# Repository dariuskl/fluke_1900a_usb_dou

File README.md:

# PCB

The latest PCB revision that has been produced and tested is rev. 0. However,
there is an error in that version: Rx and Tx are swapped (of course!) on the
USB side. That can be fixed with a bodge, but later commits fix that mistake
without making functional changes.

# Firmware

The latest firmware version that has been tested is 0.1.0.0. There are no known
issues.

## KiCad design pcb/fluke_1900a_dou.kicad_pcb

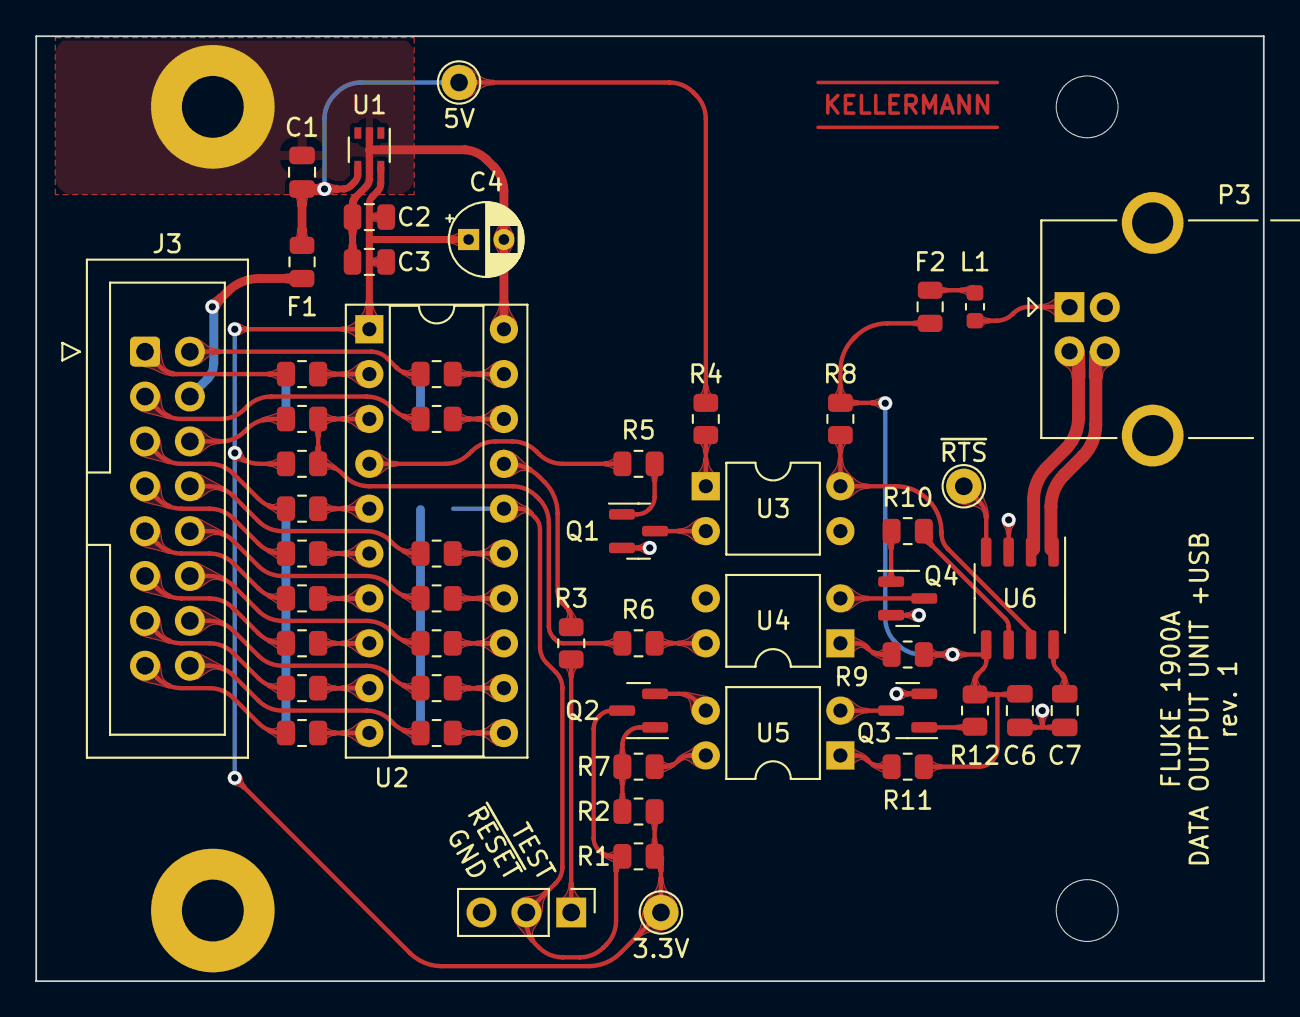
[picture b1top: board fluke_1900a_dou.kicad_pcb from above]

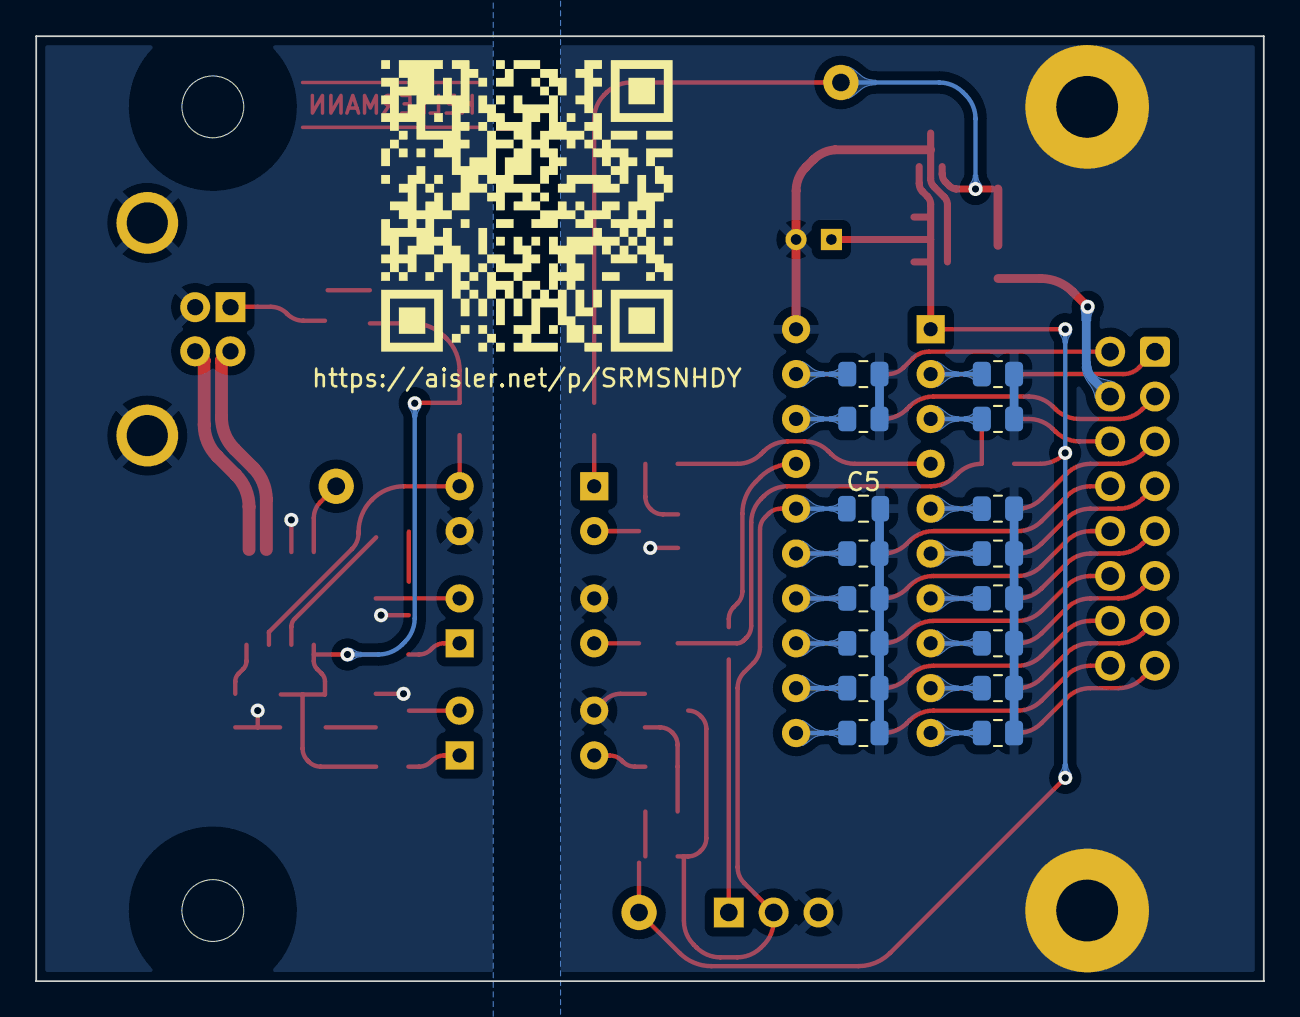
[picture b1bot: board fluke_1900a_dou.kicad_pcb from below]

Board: 2 copper layers, 69.5 x 53.5 mm, 74 parts (17 on the bottom side), 60 nets.

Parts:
C1, C3, C6, C7: 100n; C_0805_2012Metric
C2: 470n; C_0805_2012Metric
C4: 10u/10V; CP_Radial_D4.0mm_P2.00mm
C5: 2.2nF 0805; C_0805_2012Metric
F1, F2: 100mA 0805; Fuse_0805_2012Metric
H1, H2: 3,5mm; MountingHole_3.5mm_Pad
H3, H4: 3,5mm; MountingHole_3.5mm
J3: DOU CONNECTOR; IDC-Header_2x08_P2.54mm_Vertical
L1: 600R 1A 0603; L_0603_1608Metric
P3: USB_B; USB_B_OST_USB-B1HSxx_Horizontal
Q1, Q2, Q3, Q4: Si2336DS; SOT-23
QR1: https://aisler.net/p/SRMSNHDY; Aisler_QR
R1: 47k; R_0805_2012Metric
R2: 100k; R_0805_2012Metric
R3: 330; R_0805_2012Metric
R4, R9, R11: 390R 0805; R_0805_2012Metric
R5, R6, R7, R10, R12: 0; R_0805_2012Metric
R8: 4k7; R_0805_2012Metric
R13: DNP; R_0805_2012Metric
R20, R21, R22, R24, R25, R26, R27, R28, R29, R30, R31, R32, R33, R34, R35, R36, R37, R38, R39, R40, R41, R42, R43, R44, R45, R46, R47, R48, R49, R50: 1.2M 0805; R_0805_2012Metric
TP1: 5V; TestPoint_THTPad_D2.0mm_Drill1.0mm
TP2: 3.3V; TestPoint_THTPad_D2.0mm_Drill1.0mm
TP3: ~{RTS}; TestPoint_THTPad_D2.0mm_Drill1.0mm
U1: TPS71533; SOT-353_SC-70-5
U2: MSP430G2452IN20; DIP-20_W7.62mm_Socket
U3, U4, U5: SFH617A-4; DIP-4_W7.62mm
U6: CH340N; SOP-8_3.9x4.9mm_P1.27mm
X1: DEBUG; PinHeader_1x03_P2.54mm_Vertical

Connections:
+3V3: C2.1, C3.1, C4.1, R1.2, R2.2, R13.1, TP2.1, U1.5 (OUT), U2.1 (DVCC)
+5V: C1.1, F1.1, R4.1, TP1.1, U1.4 (IN)
/AS_1: R6.2, R13.2, R25.1, R45.1, U2.3 (TA0.0/CA1/A1/P1.1)
/AS_2: R27.1, R46.1, U2.15 (TDO/TDI/SDI/SDA/CAOUT/CA7/A7/P1.7)
/AS_3: R29.1, R47.1, U2.14 (TDI/TCLK/TA0.1/SDO/SCL/CA6/A6/P1.6)
/AS_4: R31.1, R48.1, U2.13 (P2.5)
/AS_5: R33.1, R49.1, U2.12 (P2.4)
/AS_6: R35.1, R50.1, U2.11 (P2.3)
/D+: P3.3 (D+), U6.1 (UD+)
/D-: P3.2 (D-), U6.2 (UD-)
/DS: R22.1, R42.1, U2.18 (P2.7/XOUT)
/OUT_A: R21.1, R44.1, U2.19 (P2.6/XIN/TA0.1)
/OUT_B: R20.2, R43.1, U2.2 (TA0CLK/ACLK/CA0/A0/P1.0)
/OUT_C: R32.2, R37.1, U2.9 (P2.1)
/OUT_D: R34.2, R36.1, U2.10 (P2.2)
/OVFL: R28.2, R39.1, U2.7 (TMS/SCLK/TA0.0/CA5/A5/P1.5)
/RESET: Q2.1 (G), R2.1, R7.2
/RNG_2: R24.2, R41.1, U2.5 (ADC10CLK/VREF-/VeREF-/CAOUT/CA3/A3/P1.3)
/RXD: R8.1, U3.4, U6.7 (RXD)
/Rx: R6.1, U4.4
/SBWTCK: R3.2, X1.1
/TXD: R10.1, U6.6 (TXD)
/Tx: R5.1, U2.4 (TA0.1/CA2/A2/P1.2)
/~ML: R26.2, R40.1, U2.6 (TCK/SMCLK/TA0.2/VREF+/VeREF+/CA4/A4/P1.4)
/~MUP: R30.2, R38.1, U2.8 (P2.0)
/~RESET: C5.1, Q2.3 (D), R1.1, U2.16 (~RST/NMI/SBWTDIO), X1.2
GND: C1.2, C2.2, C3.2, C4.2, C5.2, H1.1, H2.1, Q1.2 (S), Q2.2 (S), R36.2, R37.2, R38.2, R39.2, R40.2, R41.2, R42.2, R43.2, R44.2, R45.2, R46.2, R47.2, R48.2, R49.2, R50.2, U1.2 (GND), U2.20 (DVSS), U4.3, U5.3, X1.3
GND1: C6.1, C7.2, P3.4 (GND), P3.5 (Shield), Q3.2 (S), Q4.2 (S), U3.3, U6.3 (GND)
unnamed: C7.1, U6.8 (V3)
unnamed: F1.2, J3.4
unnamed: J3.1, R20.1
unnamed: J3.2, R21.2
unnamed: J3.3, R22.2
unnamed: J3.5, R24.1
unnamed: J3.6, R25.2
unnamed: J3.8, R27.2
unnamed: J3.9, R28.1
unnamed: J3.10, R29.2
unnamed: J3.11, R30.1
unnamed: J3.12, R31.2
unnamed: J3.13, R32.1
unnamed: J3.14, R33.2
unnamed: J3.15, R34.1
unnamed: J3.16, R35.2
unnamed: F2.1, L1.1
unnamed: L1.2, P3.1 (VBUS)
unnamed: Q1.1 (G), R5.2
unnamed: Q1.3 (D), U3.2
unnamed: Q3.1 (G), R12.2
unnamed: Q3.3 (D), U5.2
unnamed: Q4.1 (G), R10.2
unnamed: Q4.3 (D), U4.2
unnamed: R3.1, U2.17 (SBWTCK/TEST)
unnamed: R4.2, U3.1
unnamed: R7.1, U5.4
unnamed: R9.2, U4.1
unnamed: R11.2, U5.1
unnamed: J3.7, R26.1
unnamed: TP3.1, U6.4 (~RTS)
VBUS: C6.2, F2.2, R8.2, R9.1, R11.1, R12.1, U6.5 (VCC)

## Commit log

2022-04-13 initial revision of the PCB finished and ordered
2022-05-03 Tx must be connected to RXD on the CH340N
2022-05-03 add pull-up R13 to Rx line
    While the Rx line is currently not usable, it should be able to operate
    at the same bitrate as the Tx line. That requires the ability to select
    the pull-up accordingly.
2022-05-03 add fuses F1, F2 to protect device and USB host
    In case in anything ever does go wrong, the fuse should protect the
    device from any harm. The same makes sense for the USB side of things.
2022-05-13 put a comment regarding mounting
2022-05-24 add documentation for title block and various components
2022-05-24 having the .gitignore actually tracked is certainly helpful
2022-05-24 first working firmware version
2022-05-24 add a README with some helpful notes
